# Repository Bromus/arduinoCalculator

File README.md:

The arduinoCalculator is a programmable calculator. It has buttons as inputs and a display as output - maybe other sensors will be added.

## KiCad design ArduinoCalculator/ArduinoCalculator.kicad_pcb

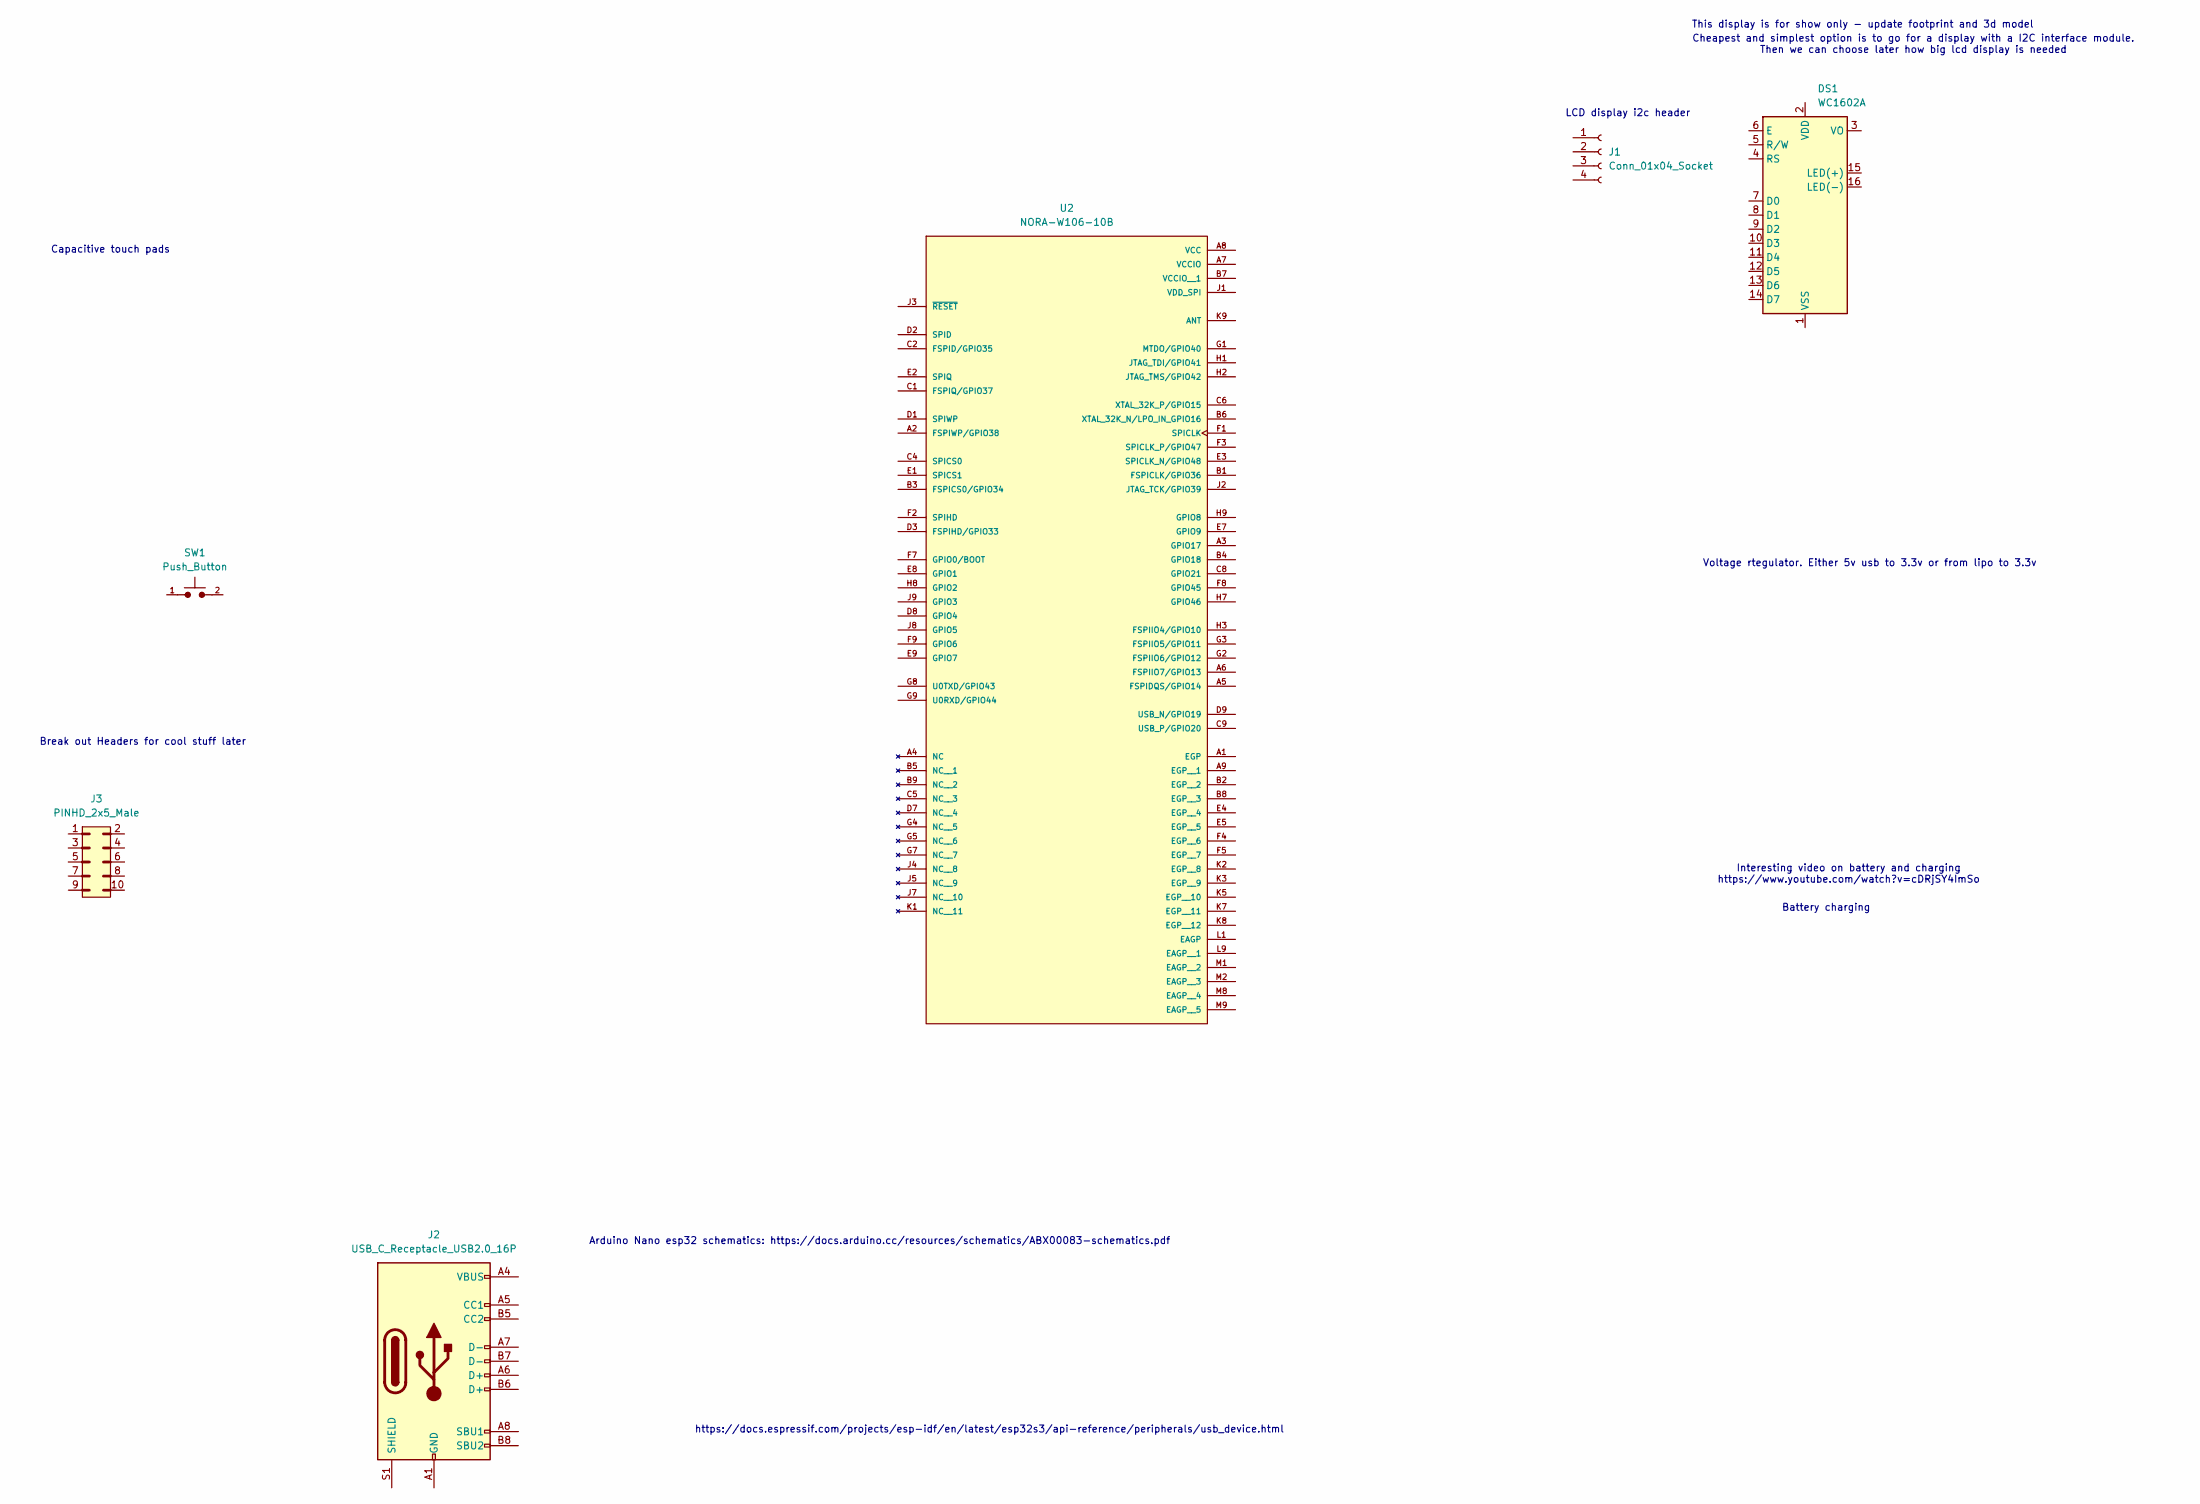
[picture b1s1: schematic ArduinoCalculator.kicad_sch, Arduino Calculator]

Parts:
DS1: WC1602A
J1: Conn_01x04_Socket; PinHeader_1x04_P2.54mm_Vertical
J2: USB_C_Receptacle_USB2.0_16P; USB_C_Receptacle_GCT_USB4105-xx-A_16P_TopMnt_Horizontal
J3: PINHD_2x5_Male; PinHeader_2x05_P2.54mm_Vertical
SW1: Push_Button; SW_Cherry_MX_PCB
U2: NORA-W106-10B; NORA-W10_UBL; PARTREV R03

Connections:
unnamed: J2.A1 (GND), J2.A12 (GND), J2.B1 (GND), J2.B12 (GND)
unnamed: J2.A4 (VBUS), J2.A9 (VBUS), J2.B4 (VBUS), J2.B9 (VBUS)

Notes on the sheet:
Battery charging
Cheapest and simplest option is to go for a display with a I2C interface module. Then we can choose later how big lcd display is needed
Break out Headers for cool stuff later
Arduino Nano esp32 schematics: https://docs.arduino.cc/resources/schematics/ABX00083-schematics.pdf
Interesting video on battery and charging https://www.youtube.com/watch?v=cDRjSY4ImSo
Capacitive touch pads
This display is for show only - update footprint and 3d model
Voltage rtegulator. Either 5v usb to 3.3v or from lipo to 3.3v
https://docs.espressif.com/projects/esp-idf/en/latest/esp32s3/api-reference/peripherals/usb_device.html
LCD display i2c header

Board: 2 copper layers, 6 parts (0 on the bottom side), 2 nets, no tracks yet.

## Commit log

2024-04-20 initial Commit - Empty kiCad project
2024-04-20 adding project structure
2024-04-20 added basic goals - written by chatgpt
2024-04-20 adding images and stuff
2024-04-20 adding drawio diagram
2024-04-20 Added Nora module to schematic
2024-04-21 added NORA model
2024-04-22 adding some schematic work
2024-04-22 adde libs
2024-04-22 slakd
